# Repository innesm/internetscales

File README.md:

# internetscales
Project to put some bathroom scales on the internet using an ESP8266

The idea here is that the MCU, an ESP8266, will use an ADC (MCP3008) to read the control lines of the LCD display of a set of bathroom scales, and upload weight readings to the internet.
The ESP8266 should be normally unpowered.
It gets woken up when stuff starts to happen on the control lines, then detects the weight reading by decoding what's displayed on the LCD.
Then, it uploads this to some cloud IoT thing and switches itself back off to save power.

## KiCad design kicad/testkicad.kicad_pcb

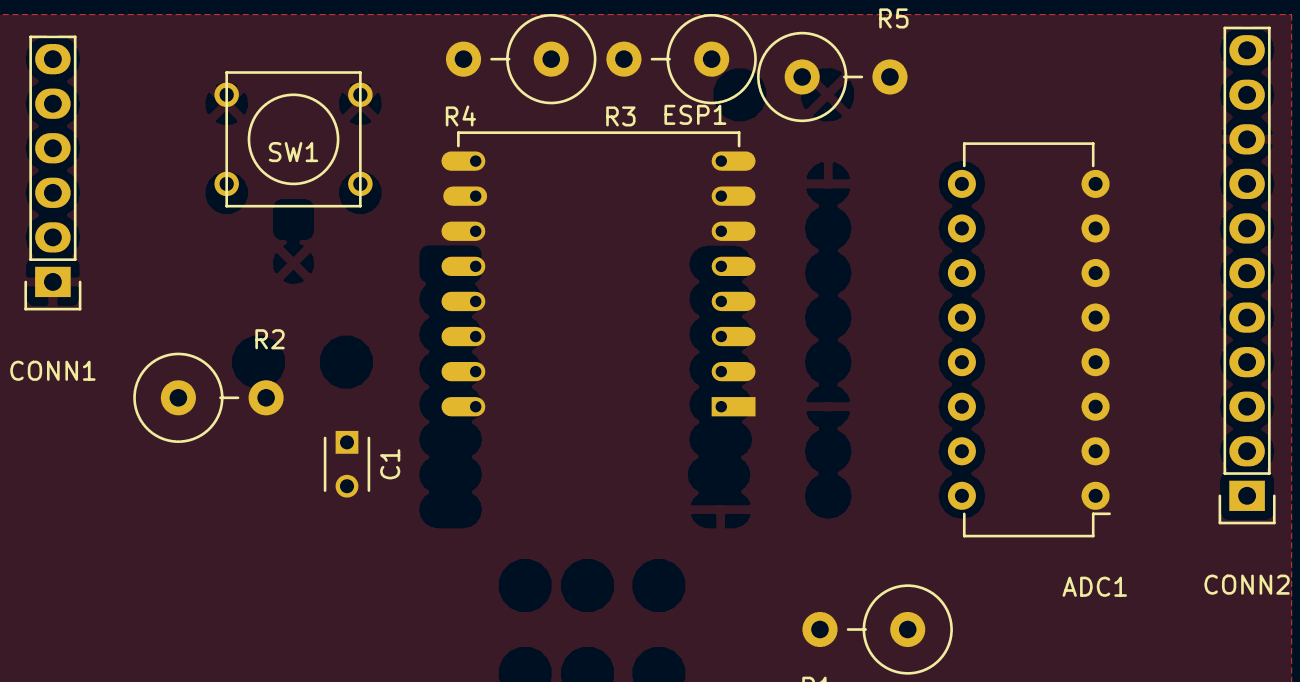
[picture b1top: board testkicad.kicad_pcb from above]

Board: 2 copper layers, 11 parts (0 on the bottom side), 20 nets, no tracks yet.

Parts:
ADC1: MCP3008; DIP-16_W7.62mm
C1: 100nF; C_Disc_D3_P2.5
CONN1: FT232; Pin_Header_Straight_1x06
CONN2: SCALES_CONN; Pin_Header_Straight_1x11
ESP1: ESP-12
R1, R2, R3, R4, R5: 10K; Resistor_Vertical_RM5mm
SW1: RESET; SW_PUSH_SMALL

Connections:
+3V3: ADC1.15, ADC1.16, CONN1.3, ESP1.8, R1.1, R2.1, R3.1, R4.1
/CH_PD: ESP1.3, R1.2
/ESP_RX: CONN1.4, ESP1.15
/ESP_TX: CONN1.5, ESP1.16
/GPIO0: ESP1.12, R3.2
/GPIO2: ESP1.11, R4.2
/GPIO15: ADC1.10, ESP1.10, R5.1
/MISO: ADC1.12, ESP1.6
/MOSI: ADC1.11, ESP1.7
/REST: C1.1, ESP1.1, R2.2, SW1.1
/SPI_CLK: ADC1.13, ESP1.5
GND: ADC1.9, ADC1.14, C1.2, CONN1.1, CONN2.9, ESP1.9, R5.2, SW1.2
unnamed: ADC1.1, CONN2.1
unnamed: ADC1.2, CONN2.2
unnamed: ADC1.3, CONN2.3
unnamed: ADC1.4, CONN2.4
unnamed: ADC1.5, CONN2.5
unnamed: ADC1.6, CONN2.6
unnamed: ADC1.7, CONN2.7
unnamed: ADC1.8, CONN2.8

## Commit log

2016-03-21 dump initial platformio attempts
2016-03-21 renamed ino to cpp - had to fix a bunch of errors.
2016-03-31 Move stuff around, and add kicad project.
2016-03-31 Re-generate netlist file after running cvpcb
2016-04-03 rename folder
2016-04-10 sleep testing
2016-04-24 add nodemcu
2016-04-24 move chip select to 4 (gpio2)
2016-04-24 comment out D1
